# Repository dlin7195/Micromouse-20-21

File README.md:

# Micromouse-20-21
Maze-solving vehicle implemented using an STM32F405RGT6 microcontroller.
The vehicle detects maze walls using readings from infrared emitter and receiver pairs.
Designed breakout board for IR receivers and emitters using EAGLE.
Uses encoder readings fed into a PID controller for distance and rotation control.

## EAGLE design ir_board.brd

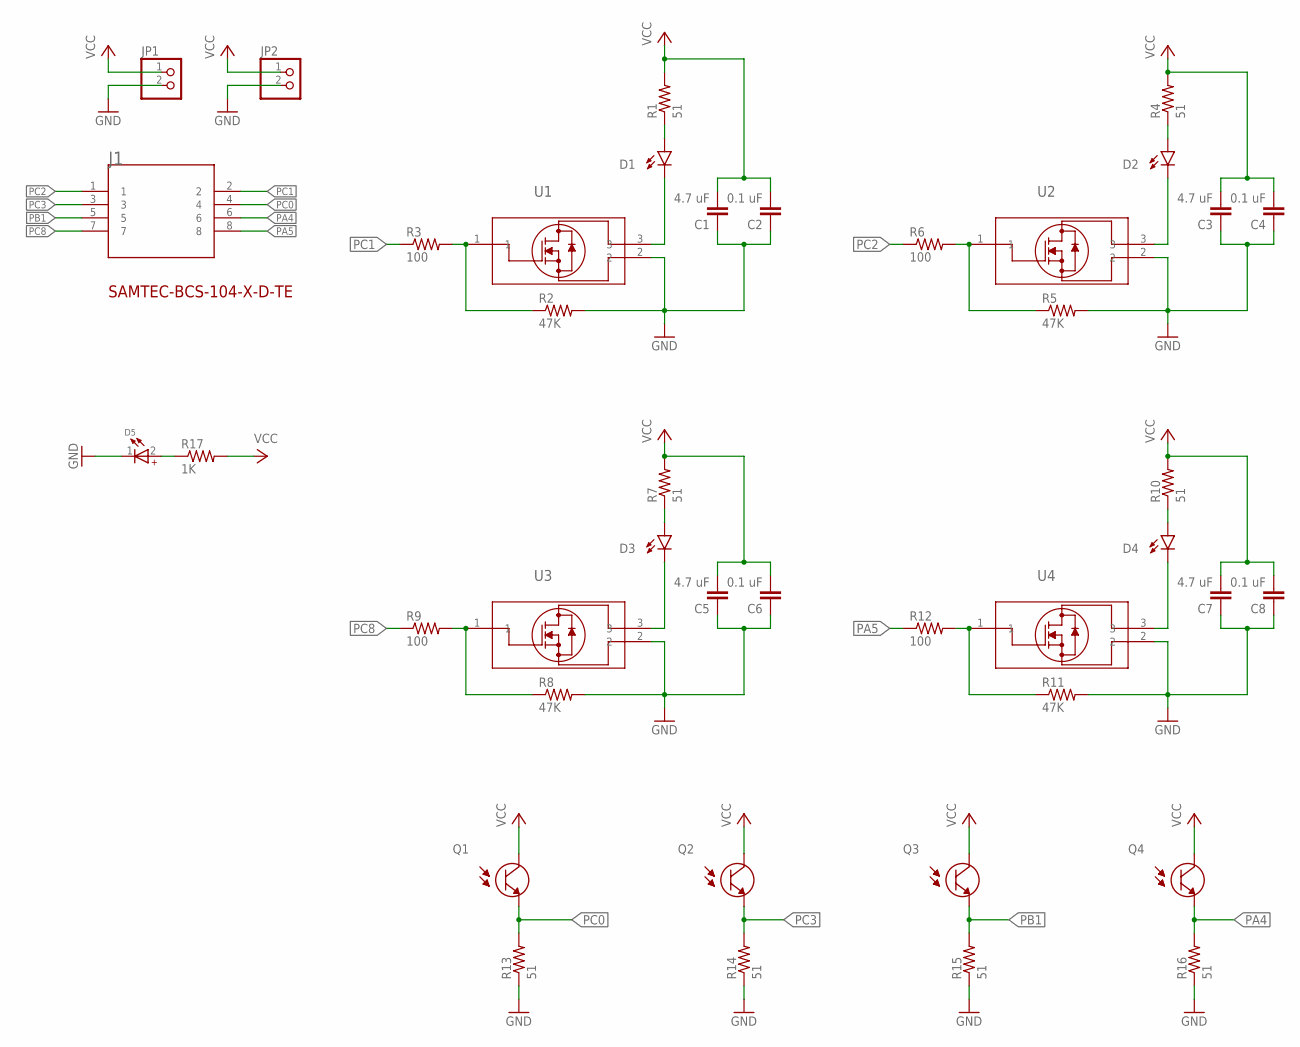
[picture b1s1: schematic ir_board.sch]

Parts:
C1, C3, C5, C7: 4.7 uF; C0805
C2, C4, C6, C8: 0.1 uF; C0805
D1, D2, D3, D4: LED5MM
D5: WL-SMCW_0805_150080BS75000; WL-SMCW_0805
J1: SAMTEC-BCS-104-X-D-TEJ; SAMTEC-BCS-104-X-D-TE
JP1, JP2: PINHD-1X2; 1X02
Q1, Q2, Q3, Q4: SFH_313_FA-3/4; XDCR_SFH_313_FA-3/4
R1, R4, R7, R10, R13, R14, R15, R16: 51; R0805
R2, R5, R8, R11: 47K; R0805
R3, R6, R9, R12: 100; R0805
R17: 1K; R0805
U1, U2, U3, U4: 2N7002LT1G; SOT-23_3L_ONS

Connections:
GND: C1.1, C2.1, C3.1, C4.1, C5.1, C6.1, C7.1, C8.1, D5.1 (-), JP1.2, JP2.2, R2.2, R5.2, R8.2, R11.2, R13.1, R14.1, R15.1, R16.1, U1.2, U2.2, U3.2, U4.2
unnamed: R2.1, R3.2, U1.1
unnamed: D1.K (C), U1.3
unnamed: D5.2 (+), R17.1
unnamed: D2.A, R4.1
unnamed: D2.K (C), U2.3
unnamed: R8.1, R9.2, U3.1
unnamed: D3.A, R7.1
unnamed: R5.1, R6.2, U2.1
unnamed: R11.1, R12.2, U4.1
unnamed: D4.K (C), U4.3
unnamed: D3.K (C), U3.3
unnamed: D4.A, R10.1
unnamed: D1.A, R1.1
PA4: J1.6, Q4.1 (E), R16.2
PA5: J1.8, R12.1
PB1: J1.5, Q3.1 (E), R15.2
PC0: J1.4, Q1.1 (E), R13.2
PC1: J1.2, R3.1
PC2: J1.1, R6.1
PC3: J1.3, Q2.1 (E), R14.2
PC8: J1.7, R9.1
VCC: C1.2, C2.2, C3.2, C4.2, C5.2, C6.2, C7.2, C8.2, JP1.1, JP2.1, Q1.2 (C), Q2.2 (C), Q3.2 (C), Q4.2 (C), R1.2, R4.2, R7.2, R10.2, R17.2

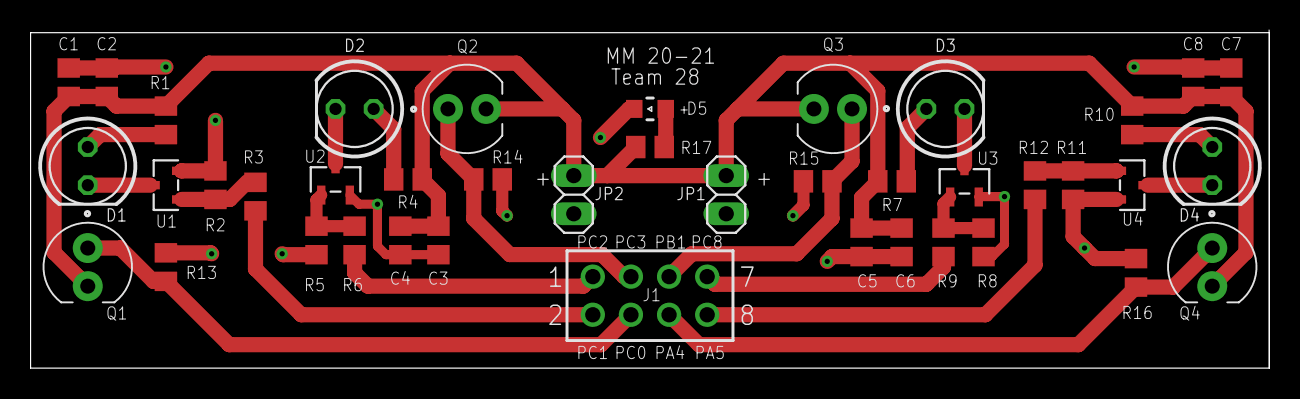
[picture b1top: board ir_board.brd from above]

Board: 2 copper layers, 82.5 x 22.5 mm, 41 parts (0 on the bottom side), 23 nets.

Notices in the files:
parts and their libraries:
Wurth_LEDs_WL-SMCW: Copyright: Würth Elektronik
COPYRIGHT: Copyright (C) 2018 Accelerated Designs. All rights reserved
